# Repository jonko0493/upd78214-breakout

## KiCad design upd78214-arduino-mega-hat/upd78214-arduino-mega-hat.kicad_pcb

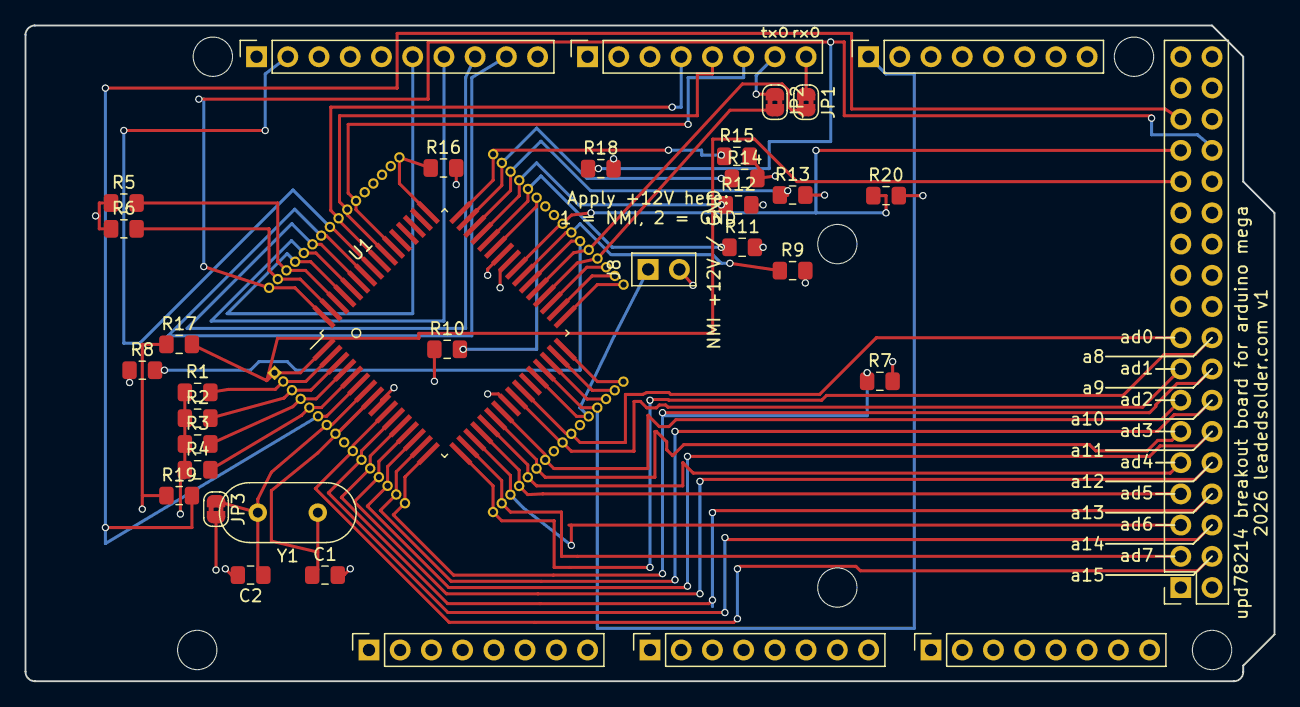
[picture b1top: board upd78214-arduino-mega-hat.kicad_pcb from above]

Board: 4 copper layers, 101.6 x 53.3 mm, 41 parts (0 on the bottom side), 54 nets.

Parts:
C1, C2: 30pF; C_0805_2012Metric_Pad1.18x1.45mm_HandSolder
J1: Power; PinSocket_1x08_P2.54mm_Vertical
J2: PWM; PinSocket_1x10_P2.54mm_Vertical
J3, J5: Analog; PinSocket_1x08_P2.54mm_Vertical
J4: PWM; PinSocket_1x08_P2.54mm_Vertical
J6: Communication; PinSocket_1x08_P2.54mm_Vertical
J7: Digital; PinSocket_2x18_P2.54mm_Vertical
J8: NMI +12V / GND; PinHeader_1x02_P2.54mm_Vertical
JP1, JP2: Jumper_2_Bridged; SolderJumper-2_P1.3mm_Bridged2Bar_RoundedPad1.0x1.5mm
JP3: SolderJumper-2; SolderJumper-2_P1.3mm_Bridged2Bar_RoundedPad1.0x1.5mm
MH1, MH2, MH3, MH4, MH5, MH6: MountingHole_3.2mm
R1, R2, R3, R4, R5, R6, R7, R8, R9, R10, R11, R12, R13, R14, R15, R16, R17, R18, R19, R20: 10k; C_0805_2012Metric_Pad1.18x1.45mm_HandSolder
U1: upd78214-64p-qfp; QFP-64_14x14_Pitch0.8mm
Y1: 4-12MHz; Crystal_HC49-U_Vertical

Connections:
+5V: J1.5, J7.35, J7.36, R17.1, R18.2, R19.1, R20.2, U1.41 (Vdd)
/NMI: J8.1, U1.28 (p2,0/nmi)
/RX0/0: J4.8, JP1.1 (A)
/SCL/21: J2.1, J6.8
/TX0/1: J4.7, JP2.1 (A)
/a0: J4.6, U1.54 (p0,0)
/a1: J4.5, U1.55 (p0,1)
/a2: J4.4, U1.56 (p0,2)
/a3: J2.2, U1.57 (p0,3)
/a4: J2.9, U1.58 (p0,4)
/a5: J2.8, U1.59 (p0,5)
/a6: J2.7, U1.60 (p0,6)
/a7: J2.6, U1.61 (p0,7)
/a8: J7.18, U1.17 (p5,0/a8)
/a9: J7.16, R7.1, U1.16 (p5,1/a9)
/a10: J7.14, U1.15 (p5,2/a10)
/a11: J7.12, U1.14 (p5,3/a11)
/a12: J7.10, U1.13 (p5,4/a12)
/a13: J7.8, U1.12 (p5,5/a13)
/a14: J7.6, U1.11 (p5,6/a14)
/a15: J7.4, U1.10 (p5,7/a15)
/ad0: J7.17, U1.26 (p4,0/ad0)
/ad1: J7.15, U1.25 (p4,1/ad1)
/ad2: J7.13, U1.23 (p4,2/ad2)
/ad3: J7.11, U1.22 (p4,3/ad3)
/ad4: J7.9, U1.21 (p4,4/ad4)
/ad5: J7.7, U1.20 (p4,5/ad5)
/ad6: J7.5, U1.19 (p4,6/ad6)
/ad7: J7.3, U1.18 (p4,7/ad7)
/pd02: R1.2, U1.2 (p6,3/a19)
/pd03: R2.2, U1.3 (p6,2/a18)
/pd04: R3.2, U1.4 (p6,1/a17)
/pd05: R4.2, U1.5 (p6,0/a16)
/pd38: R8.2, U1.38 (p3,2/sck)
/pd39: R9.1, U1.39 (p3,3/so/sb0)
/pd43: R10.2, U1.43 (AVref)
/pd44: R11.1, U1.44 (p7,5/AN5)
/pd45: R12.1, U1.45 (p7,4/AN4)
/pd46: R13.1, U1.46 (p7,3/AN3)
/pd47: R14.1, U1.47 (p7,2/AN2)
/pd48: R15.1, U1.48 (p7,1/AN1)
/pd49: R16.1, U1.49 (p7,0/AN0)
/pd62: R5.2, U1.62 (p6,7/~REFRQ/AN7)
/pd63: R6.2, U1.63 (p6,6/~WAIT/AN6)
/prog_a9: J6.1, U1.29 (p2,1/intp0)
/upd_ce: J7.30, R18.1, U1.64 (p6,5/~WR)
/upd_ea: J7.29, R20.1, U1.40 (~EA)
/upd_oe: J7.27, R17.2, U1.1 (p6,4/~RD)
/upd_reset: J7.31, R19.2, U1.6 (~RESET)
GND: C1.2, C2.2, J1.6, J1.7, J2.4, J7.1, J7.2, J8.2, JP3.2 (B), R1.1, R2.1, R3.1, R4.1, R5.1, R6.1, R7.2, R8.1, R9.2, R10.1, R11.2, R12.2, R13.2, R14.2, R15.2, R16.2, U1.9 (Vss), U1.24 (Vss), U1.30 (p2,2/intp1), U1.31 (p2,3/intp2/ci), U1.32 (p2,4/intp3), U1.33 (p2,5/intp4/asck), U1.34 (p2,6/intp5), U1.35 (p2,7/si), U1.42 (AVss)
unnamed: JP1.2 (B), U1.37 (p3,1/txd)
unnamed: JP2.2 (B), U1.36 (p3,0/rxd)
unnamed: C1.1, U1.8 (X1), Y1.1
unnamed: C2.1, JP3.1 (A), U1.7 (X2), Y1.2

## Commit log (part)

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2022-09-19 Add attempt at PCB
